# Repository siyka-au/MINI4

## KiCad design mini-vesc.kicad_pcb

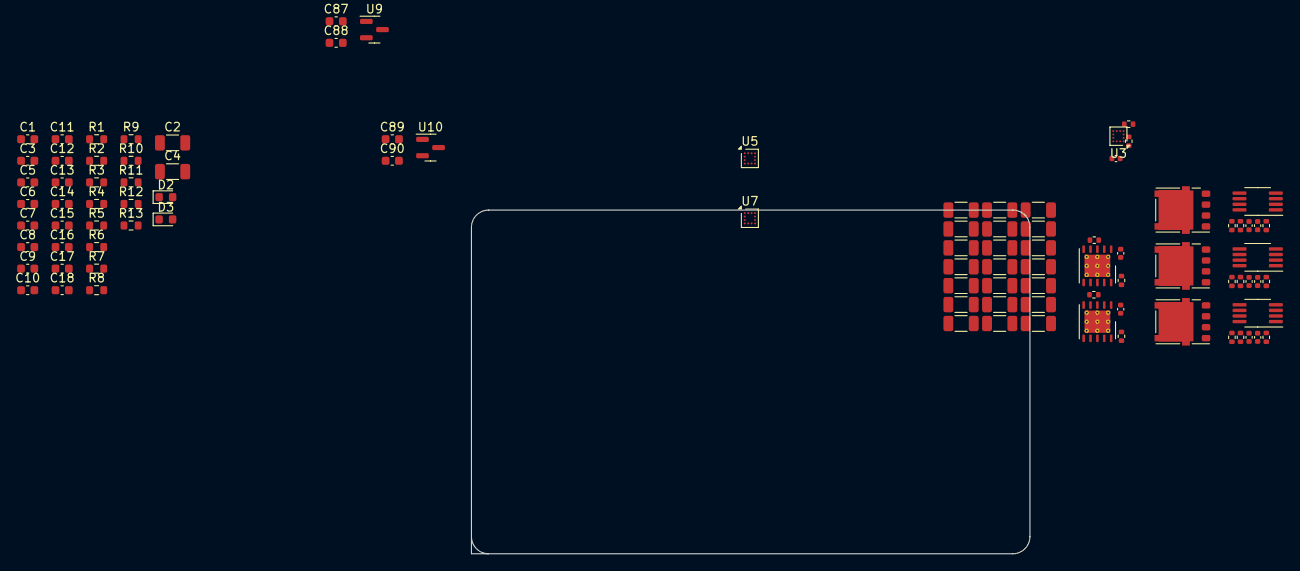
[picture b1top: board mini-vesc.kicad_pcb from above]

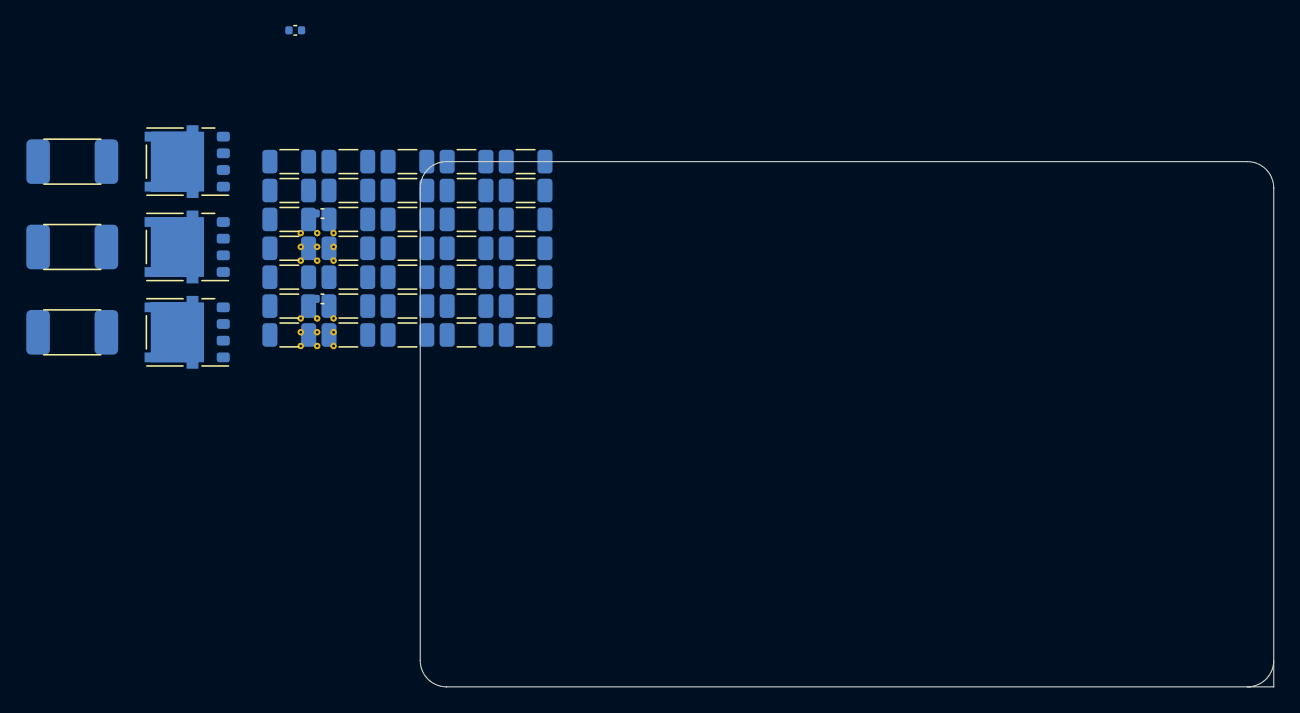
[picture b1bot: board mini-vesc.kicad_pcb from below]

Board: 4 copper layers, 65.0 x 40.0 mm, 139 parts (44 on the bottom side), 44 nets, no tracks yet.

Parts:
C1: 220nF; C_0603_1608Metric
C2, C19, C20, C21, C22, C23, C24, C25, C26, C27, C28, C29, C30, C31, C32, C33, C34, C35, C36, C37, C38, C39, C40, C41, C42, C43, C44, C45, C46, C47, C48, C49, C50, C51, C52, C53, C54, C55, C56, C57, C58, C59, C60, C61, C62, C63, C64, C65, C66, C67, C68, C69, C70, C71, C72, C73, C74: 2.2µF; C_1206_3216Metric
C3, C5, C6, C7, C8, C9, C15, C16: 100nF; C_0603_1608Metric
C4: 10µF; C_1206_3216Metric
C10, C11, C13, C14, C18, C87, C88, C89, C90: 2.2µF; C_0603_1608Metric
C12, C17: 10pF; C_0603_1608Metric
C75, C77, C79, C81, C83, C85: 2.2µF; C_0402_1005Metric
C76, C80, C84: 470nF; C_0402_1005Metric
C78, C82, C86: 4.7nF; C_0402_1005Metric
D2, D3: LED; LED_0603_1608Metric
Q1, Q2, Q3, Q4, Q5, Q6: NTMFS5C604NLT1G; ONSemi_SO-8FL_488AA
R1, R9, R10, R11: 10kΩ; R_0603_1608Metric
R2: 54.9kΩ; R_0603_1608Metric
R3: 100kΩ; R_0603_1608Metric
R4: 100Ω; R_0603_1608Metric
R5: 39kΩ; R_0603_1608Metric
R6: 2.2kΩ; R_0603_1608Metric
R7, R8: 220Ω; R_0603_1608Metric
R12, R13: 22Ω; R_0603_1608Metric
R15, R16, R22, R23, R29, R30: 3.9Ω; R_0402_1005Metric
R17, R24, R31: 39kΩ; R_0402_1005Metric
R18, R25, R32: 2.2kΩ; R_0402_1005Metric
R19, R26, R33: 500µΩ; R_Shunt_Bourns_CSS2H-2512_6332Metric
R20, R27, R34: 100Ω; R_0402_1005Metric
U3, U5#2, U7: LMG1205; Texas_YFX0012_DSBGA-12_1.76x1.91mm_Layout3x4_P0.4mm
U4, U6, U8: AD8417; MSOP-8_3x3mm_P0.65mm
U5, U7#2: LM5113-Q1; WSON-10-1EP_4x4mm_P0.8mm_EP2.6x3mm_ThermalVias
U9, U10: MCP1700x-330xxTT; SOT-23

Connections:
+5V: C4.2, C75.1, C79.1, C83.1, C87.1, C89.1, R2.1, U3.A3 (V_{dd}), U3.C4 (V_{dd}), U5.1 (V_{dd}), U5#2.A3 (V_{dd}), U5#2.C4 (V_{dd}), U7.A3 (V_{dd}), U7.C4 (V_{dd}), U7#2.1 (V_{dd}), U9.3 (VI), U10.3 (VI)
/Half Bridge U/HighGate: Q1.4 (G), R15.1, U3.D1 (HOL)
/Half Bridge U/LowGate: Q2.4 (G), R16.2, U3.A1 (LOL)
/Half Bridge V/HighGate: Q5.4 (G), R29.1, U7.D1 (HOL), U7#2.4 (HOL)
/Half Bridge V/LowGate: Q6.4 (G), R30.2, U7.A1 (LOL), U7#2.9 (LOL)
/Half Bridge W/HighGate: Q3.4 (G), R22.1, U5.4 (HOL), U5#2.D1 (HOL)
/Half Bridge W/LowGate: Q4.4 (G), R23.2, U5.9 (LOL), U5#2.A1 (LOL)
/U: R19.1, U4.1 (IN-)
/V: R33.1, U8.1 (IN-)
/W: R26.1, U6.1 (IN-)
HI2: U7.B4 (HI), U7#2.6 (HI)
HI3: U5.6 (HI), U5#2.B4 (HI)
HS: C76.2, C80.2, C84.2, Q1.1 (S), Q1.2 (S), Q1.3 (S), Q2.5 (D), Q3.1 (S), Q3.2 (S), Q3.3 (S), Q4.5 (D), Q5.1 (S), Q5.2 (S), Q5.3 (S), Q6.5 (D), R17.2, R19.2, R24.2, R26.2, R31.2, R33.2, U3.C1 (HS), U3.D4 (HS), U4.8 (IN+), U5#2.C1 (HS), U5#2.D4 (HS), U6.8 (IN+), U7.C1 (HS), U7.D4 (HS), U8.8 (IN+)
I_{senseU}: C78.2, R20.2
I_{senseV}: C86.2, R34.2
I_{senseW}: C82.2, R27.2
LI2: U7.A4 (LI), U7#2.7 (LI)
LI3: U5.7 (LI), U5#2.A4 (LI)
unnamed: D2.1 (K), R7.2
unnamed: D3.1 (K), R8.2
unnamed: R1.2, R2.2
unnamed: C10.2, R10.2, R11.2
unnamed: C76.1, U3.D3 (HB)
unnamed: R15.2, U3.D2 (HOH)
unnamed: R16.1, U3.B1 (LOH)
unnamed: R20.1, U4.5 (OUT)
unnamed: C80.1, U5.2 (HB), U5#2.D3 (HB)
unnamed: R22.2, U5.3 (HOH), U5#2.D2 (HOH)
unnamed: R23.1, U5.10 (LOH), U5#2.B1 (LOH)
unnamed: R27.1, U6.5 (OUT)
unnamed: C84.1, U7.D3 (HB), U7#2.2 (HB)
unnamed: R29.2, U7.D2 (HOH), U7#2.3 (HOH)
unnamed: R30.1, U7.B1 (LOH), U7#2.10 (LOH)
unnamed: R34.1, U8.5 (OUT)
SERVO: C3.2, R4.2
Supply_{sense}: R5.2, R6.2
TEMP_MOTOR: C11.2, R9.2
VAA: C16.1, C18.1, C77.2, C81.2, C85.2, C90.1, R9.1, R11.1, U4.6 (VS), U4.7 (REF1), U6.6 (VS), U6.7 (REF1), U8.6 (VS), U8.7 (REF1), U10.2 (VO)
VCC: C5.1, C6.1, C7.1, C8.1, C9.1, C88.1, U9.2 (VO)
VDD: C2.2, C19.1, C20.1, C21.1, C22.1, C23.1, C24.1, C25.1, C26.1, C27.1, C28.1, C29.1, C30.1, C31.1, C32.1, C33.1, C34.1, C35.1, C36.1, C37.1, C38.1, C39.1, C40.1, C41.1, C42.1, C43.1, C44.1, C45.1, C46.1, C47.1, C48.1, C49.1, C50.1, C51.1, C52.1, C53.1, C54.1, C55.1, C56.1, C57.1, C58.1, C59.1, C60.1, C61.1, C62.1, C63.1, C64.1, C65.1, C66.1, C67.1, C68.1, C69.1, C70.1, C71.1, C72.1, C73.1, C74.1, Q1.5 (D), Q3.5 (D), Q5.5 (D), R3.1, R5.1
VSS: C2.1, C3.1, C4.1, C5.2, C6.2, C7.2, C8.2, C9.2, C10.1, C11.1, C12.2, C13.1, C14.1, C15.1, C16.2, C17.2, C18.2, C19.2, C20.2, C21.2, C22.2, C23.2, C24.2, C25.2, C26.2, C27.2, C28.2, C29.2, C30.2, C31.2, C32.2, C33.2, C34.2, C35.2, C36.2, C37.2, C38.2, C39.2, C40.2, C41.2, C42.2, C43.2, C44.2, C45.2, C46.2, C47.2, C48.2, C49.2, C50.2, C51.2, C52.2, C53.2, C54.2, C55.2, C56.2, C57.2, C58.2, C59.2, C60.2, C61.2, C62.2, C63.2, C64.2, C65.2, C66.2, C67.2, C68.2, C69.2, C70.2, C71.2, C72.2, C73.2, C74.2, C75.2, C77.1, C78.1, C79.2, C81.1, C82.1, C83.2, C85.1, C86.1, C87.2, C88.2, C89.2, C90.2, Q2.1 (S), Q2.2 (S), Q2.3 (S), Q4.1 (S), Q4.2 (S), Q4.3 (S), Q6.1 (S), Q6.2 (S), Q6.3 (S), R1.1, R6.1, R7.1, R8.1, R10.1, R18.1, R25.1, R32.1, U3.A2 (V_{ss}), U4.2 (GND), U4.3 (REF2), U5.8 (V_{ss}), U5.11 (EP), U5#2.A2 (V_{ss}), U6.2 (GND), U6.3 (REF2), U7.A2 (V_{ss}), U7#2.8 (V_{ss}), U7#2.11 (EP), U8.2 (GND), U8.3 (REF2), U9.1 (GND), U10.1 (GND)
V_{senseU}: R17.1, R18.2
V_{senseV}: R31.1, R32.2
V_{senseW}: R24.1, R25.2

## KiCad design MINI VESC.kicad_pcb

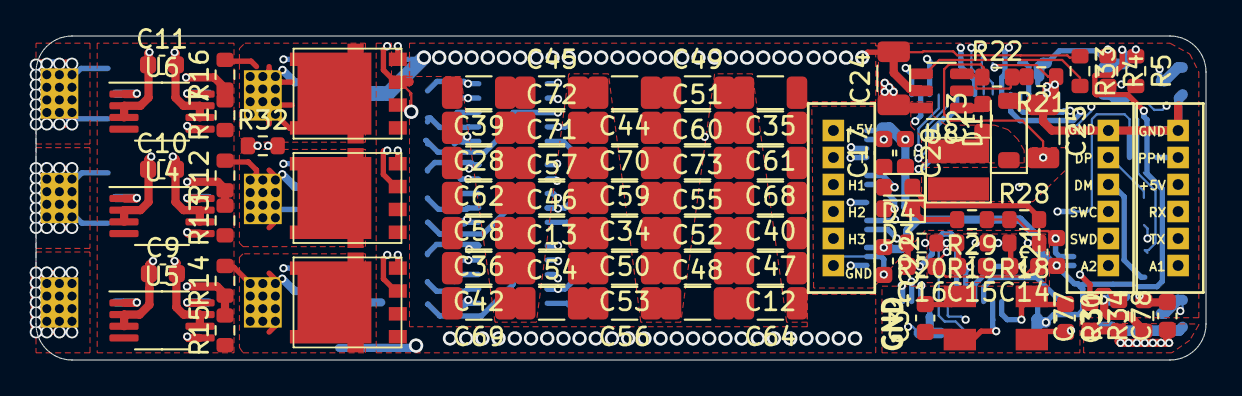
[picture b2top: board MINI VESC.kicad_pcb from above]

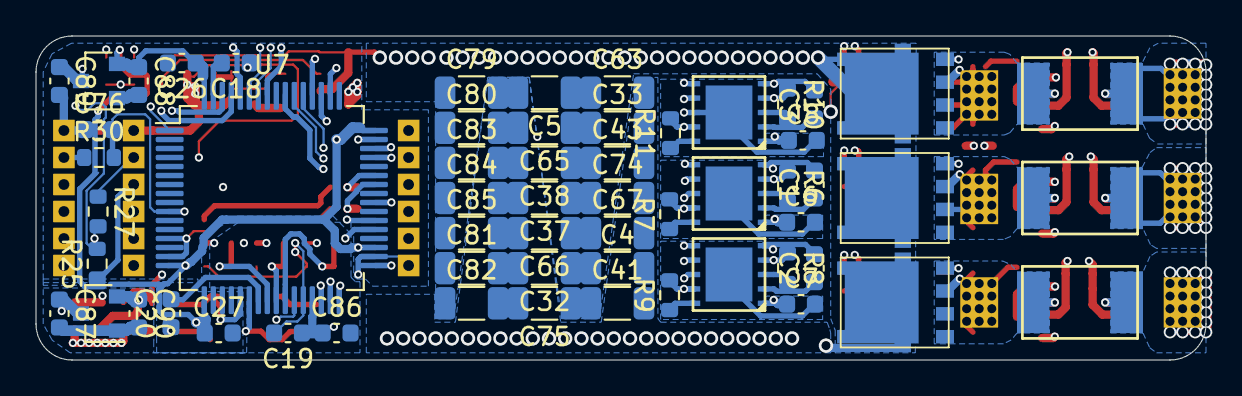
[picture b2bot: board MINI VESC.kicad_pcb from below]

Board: 4 copper layers, 65.0 x 18.0 mm, 151 parts (59 on the bottom side), 60 nets.

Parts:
C1, C2, C3: 470n; C_0603_1608Metric
C4, C5, C12, C13, C25, C28, C32, C39, C48, C60, C61, C62, C63, C74, C75, C79, C80, C82, C84, C85: 10u; C_1206_3216Metric
C6, C7, C8, C9, C10, C11, C17, C18, C77, C78, C86, C87, C88, C89, C90: 2u2; C_0603_1608Metric
C14, C15, C16: 4n7; C_0603_1608Metric
C19, C20, C21, C22, C26, C27, C29, C76: 100n; C_0603_1608Metric
C23: 220nF; C_0603_1608Metric
C24: 2u2; C_1206_3216Metric
C30, C31: 10pF; C_0603_1608Metric
C33, C34, C35, C36, C37, C38, C40, C41, C42, C43, C44, C45, C46, C47, C49, C50, C51, C52, C53, C54, C55, C56, C57, C58, C59, C64, C65, C66, C67, C68, C69, C70, C71, C72, C73, C81, C83: C; C_1206_3216Metric
D1: D_Schottky; D_SOD-123
D3, D4: LED; LED_0603_1608Metric
L1: Wurth Electronics 74438335220; WE-MAPI
P1, P2, P3, P4, P5, P6: CONN_1; prekov
P9, P10, P11: CONN_01X06; JST_ZH_1.5_6-Pin
Q1, Q2, Q3, Q4, Q5, Q6: NTMFS5C604NLT1G; DFN5
R1, R2, R3: R0005; 2512Rv2
R4, R12, R14: 39k; R_0603_1608Metric
R5, R13, R15, R17: 2k2; R_0603_1608Metric
R6, R7, R8, R9, R10, R11: 3R9; R_0603_1608Metric
R16: 25k5; R_0603_1608Metric
R18, R19, R20, R30: 100R; R_0603_1608Metric
R21, R31, R34: 10k; R_0603_1608Metric
R22: 54k9; R_0603_1608Metric
R25, R27: 22R; R_0603_1608Metric
R28, R29: 220R; R_0603_1608Metric
R32: 10kNTC; R_0603_1608Metric
R33: 100k; R_0603_1608Metric
U1, U2, U3: LM5113; WSON10_
U4, U5, U6: AD8418; MSOP-8_3x3mm_P0.65mm
U7: STM32F40X_LQFP64; LQFP-64_10x10mm_P0.5mm
U8: LMR16006; SOT-23-6
U9, U10: MCP1700; SOT-23
X1: ABM3B-8.000MHZ; 5x3.2KRISTALL

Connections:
+5V: C6.1, C7.1, C8.1, C25.2, C87.1, C89.1, L1.2, P9.1, P11.4, R22.1, U1.1, U2.1, U3.1, U9.3 (VI), U10.3 (VI)
ADC_EXT1: P11.1, U7.21
ADC_EXT2: P10.1, U7.22
C1: C14.2, R18.2, U7.8
C2: C15.2, R19.2, U7.9
C3: C16.2, R20.2, U7.10
EN: R33.2, U8.4
HALL_1: P9.3, U7.37
HALL_2: P9.4, U7.38
HALL_3: P9.5, U7.39
HI1: U1.6, U7.41
HI2: U2.6, U7.42
HI3: U3.6, U7.43
I1: R18.1, U4.5
I2: R19.1, U5.5
I3: R20.1, U6.5
LED_GREEN: D3.2 (A), U7.26
LED_RED: D4.2 (A), U7.27
LI1: U1.7, U7.34
LI2: U2.7, U7.35
LI3: U3.7, U7.36
unnamed: D1.1, U8.6
unnamed: C23.1, L1.1
unnamed: D3.1 (K), R29.2
unnamed: D4.1 (K), R28.2
unnamed: P10.4, R25.1
unnamed: P10.5, R27.1
unnamed: Q1.1 (G), R6.1
unnamed: Q2.1 (G), R7.2
unnamed: Q3.1 (G), R8.1
unnamed: Q4.1 (G), R9.2
unnamed: Q5.1 (G), R10.1
unnamed: Q6.1 (G), R11.2
unnamed: P1.1, R1.1
unnamed: P2.1, R2.1
unnamed: P3.1, R3.1
unnamed: C77.2, R31.2, R32.2
unnamed: C30.1, X1.1
unnamed: C31.1, X1.2
unnamed: R21.2, R22.2
RX: P11.3, U7.30
SENS_1: R12.1, R13.2, U7.14
SENS_2: R14.1, R15.2, U7.15
SENS_3: R16.1, R17.2, U7.16
SENS_SUPPLY: R4.2, R5.2, U7.11
SERVO: C76.2, R30.2, U7.58
SH1: C1.2, P4.1, Q1.2 (S), Q2.3 (D), R1.2, R12.2, U1.5, U4.8
SH2: C2.2, P5.1, Q3.2 (S), Q4.3 (D), R2.2, R14.2, U2.5, U5.8
SH3: C3.2, P6.1, Q5.2 (S), Q6.3 (D), R3.2, R16.2, U3.5, U6.8
SWCLK: P10.3, U7.49
SWDIO: P10.2, U7.46
TEMP_MOTOR: C78.2, P9.2, R34.2, U7.24
TX: P11.2, U7.29
USB-DM: R25.2, U7.44
USB-DP: R27.2, U7.45
VAA: C9.2, C10.2, C11.2, C19.1, C86.1, C90.1, R32.1, R34.1, U4.6, U4.7, U5.6, U5.7, U6.6, U6.7, U7.13, U10.2 (VO)
VCC: C21.1, C22.1, C26.1, C27.1, C29.1, C88.1, U7.1, U7.19, U7.32, U7.48, U7.64, U9.2 (VO)
VDD: C4.1, C5.1, C12.1, C13.1, C24.2, C28.1, C32.1, C33.1, C34.1, C35.1, C36.1, C37.1, C38.1, C39.1, C40.1, C41.1, C42.1, C43.1, C44.1, C45.1, C46.1, C47.1, C48.1, C49.1, C50.1, C51.1, C52.1, C53.1, C54.1, C55.1, C56.1, C57.1, C58.1, C59.1, C60.1, C61.1, C62.1, C63.1, C64.1, C65.1, C66.1, C67.1, C68.1, C69.1, C70.1, C71.1, C72.1, C73.1, C74.1, C75.1, C79.1, C80.1, C81.1, C82.1, C83.1, C84.1, C85.1, Q1.3 (D), Q3.3 (D), Q5.3 (D), R4.1, R33.1, U8.5
VSS: C4.2, C5.2, C6.2, C7.2, C8.2, C9.1, C10.1, C11.1, C12.2, C13.2, C14.1, C15.1, C16.1, C17.1, C18.1, C19.2, C20.1, C21.2, C22.2, C24.1, C25.1, C26.2, C27.2, C28.2, C29.2, C30.2, C31.2, C32.2, C33.2, C34.2, C35.2, C36.2, C37.2, C38.2, C39.2, C40.2, C41.2, C42.2, C43.2, C44.2, C45.2, C46.2, C47.2, C48.2, C49.2, C50.2, C51.2, C52.2, C53.2, C54.2, C55.2, C56.2, C57.2, C58.2, C59.2, C60.2, C61.2, C62.2, C63.2, C64.2, C65.2, C66.2, C67.2, C68.2, C69.2, C70.2, C71.2, C72.2, C73.2, C74.2, C75.2, C76.1, C77.1, C78.1, C79.2, C80.2, C81.2, C82.2, C83.2, C84.2, C85.2, C86.2, C87.2, C88.2, C89.2, C90.2, D1.2, P9.6, P10.6, P11.6, Q2.2 (S), Q4.2 (S), Q6.2 (S), R5.1, R13.1, R15.1, R17.1, R21.1, R28.1, R29.1, R31.1, U1.8, U2.8, U3.8, U4.2, U4.3, U5.2, U5.3, U6.2, U6.3, U7.12, U7.18, U7.60, U7.63, U8.2, U9.1 (GND), U10.1 (GND), X1.3 (case)
servoi: P11.5, R30.1

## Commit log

2024-03-04 Migrating to KiCAD 7
2024-03-04 Lots of stuff
2024-03-05 More work
2024-03-05 Tidy up
2024-03-05 Renaming files
2024-03-07 Playing around with routing
2024-03-07 Playing with routing some more, trying to determine board size
2024-03-11 Did something I think?
2024-03-11 Removed log files and updated gitignore
